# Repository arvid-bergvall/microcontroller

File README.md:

Basic microcontroller design using stm32f103t8c6 chip

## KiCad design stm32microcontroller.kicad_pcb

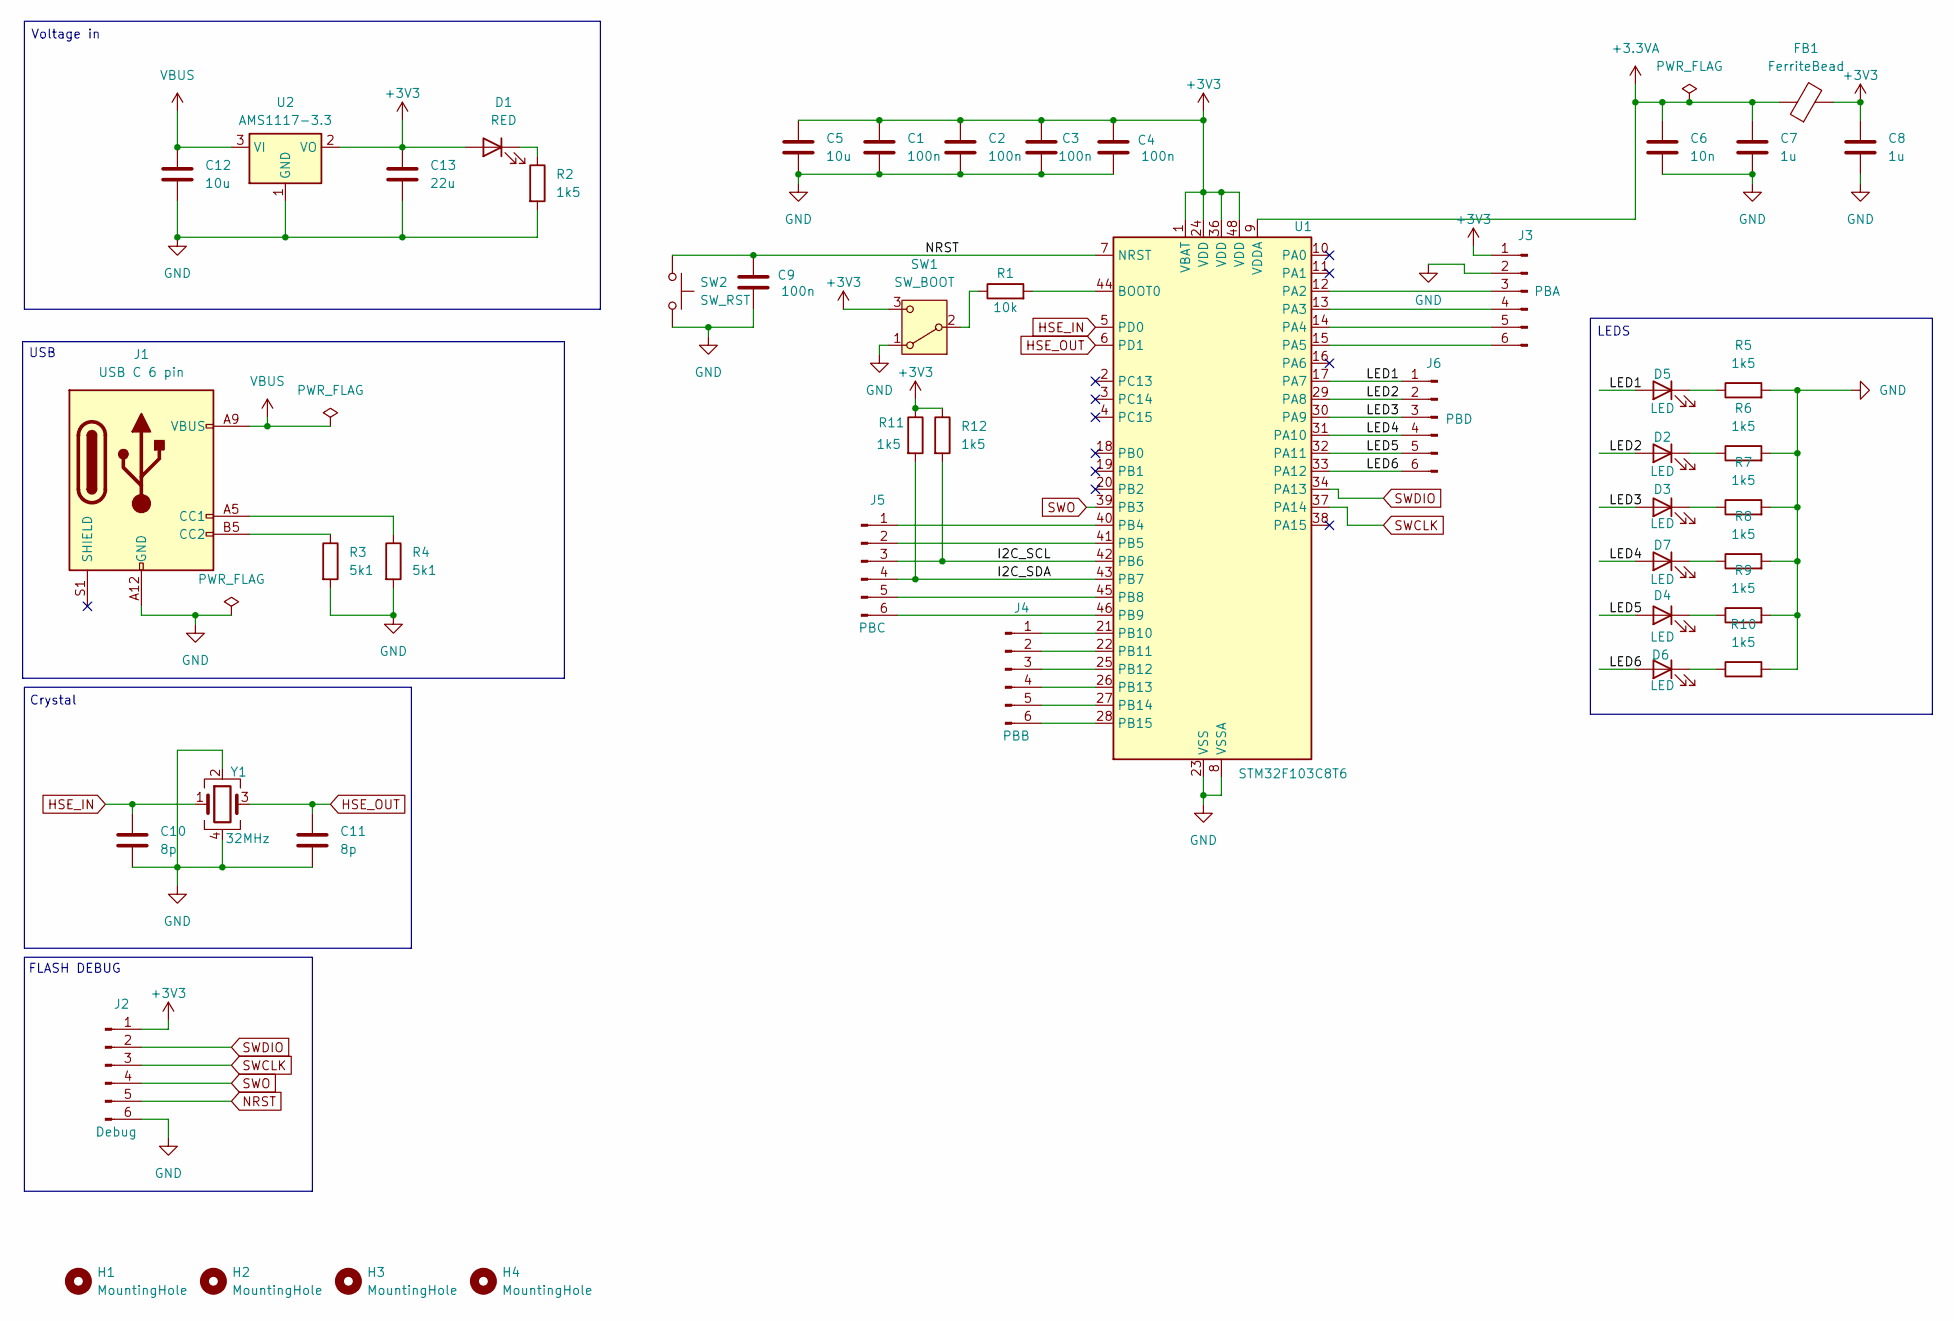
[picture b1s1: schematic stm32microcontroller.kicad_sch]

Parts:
C1, C2, C3, C4, C9: 100n; C_0603_1608Metric
C5, C12: 10u; C_0603_1608Metric
C6: 10n; C_0603_1608Metric
C7, C8: 1u; C_0603_1608Metric
C10, C11: 8p; C_0603_1608Metric
C13: 22u; C_0603_1608Metric
D1: RED; LED_0603_1608Metric
D2, D3, D4, D5, D6, D7: LED; LED_0603_1608Metric
FB1: FerriteBead; R_0805_2012Metric
H1, H2, H3, H4: MountingHole; MountingHole_2.2mm_M2
J1: USB C 6 pin; USB_C_Receptacle_GCT_USB4125-xx-x_6P_TopMnt_Horizontal
J2: Debug; PinHeader_2x03_P2.54mm_Vertical
J3: PBA; PinHeader_1x06_P2.54mm_Vertical
J4: PBB; PinHeader_1x06_P2.54mm_Vertical
J5: PBC; PinHeader_1x06_P2.54mm_Vertical
J6: PBD; PinHeader_1x06_P2.54mm_Vertical
R1: 10k; R_0603_1608Metric
R2, R5, R6, R7, R8, R9, R10, R11, R12: 1k5; R_0603_1608Metric
R3, R4: 5k1; R_0603_1608Metric
SW1: SW_BOOT; PinHeader_1x03_P2.54mm_Vertical
SW2: SW_RST; SW_DIP_SPSTx01_Slide_Copal_CHS-01A_W5.08mm_P1.27mm_JPin
U1: STM32F103C8T6; LQFP-48_7x7mm_P0.5mm
U2: AMS1117-3.3; SOT-223-3_TabPin2
Y1: 32MHz; Oscillator_SMD_Abracon_ASCO-4Pin_1.6x1.2mm

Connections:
+3.3VA: C6.1, C7.1, FB1.1, U1.9 (VDDA)
+3V3: C1.1, C2.1, C3.1, C4.1, C5.1, C8.1, C13.1, D1.2 (A), FB1.2, J2.1, J3.1, R11.1, R12.1, SW1.3 (C), U1.1 (VBAT), U1.24 (VDD), U1.36 (VDD), U1.48 (VDD), U2.2 (VO); also elsewhere on the board
/I2C_SCL: J5.3, R12.2, U1.42 (PB6)
/I2C_SDA: J5.4, R11.2, U1.43 (PB7)
/LED1: D5.2 (A), J6.1, U1.17 (PA7)
/LED2: D2.2 (A), J6.2, U1.29 (PA8)
/LED3: D3.2 (A), J6.3, U1.30 (PA9)
/LED4: D7.2 (A), J6.4, U1.31 (PA10)
/LED5: D4.2 (A), J6.5, U1.32 (PA11)
/LED6: D6.2 (A), J6.6, U1.33 (PA12)
GND: C1.2, C2.2, C3.2, C4.2, C5.2, C6.2, C7.2, C8.2, C9.2, C10.2, C11.2, C12.2, C13.2, J1.A12 (GND), J1.B12 (GND), J2.6, J3.2, R2.2, R3.2, R4.2, R5.2, R6.2, R7.2, R8.2, R9.2, R10.2, SW1.1 (A), SW2.2, U1.8 (VSSA), U1.23 (VSS), U1.35 (VSS), U1.47 (VSS), U2.1 (GND), Y1.2, Y1.4; also elsewhere on the board
HSE_IN: C10.1, U1.5 (PD0), Y1.1
HSE_OUT: C11.1, U1.6 (PD1), Y1.3
NRST: C9.1, SW2.1, U1.7 (NRST); also elsewhere on the board
unnamed: D1.1 (K), R2.1
unnamed: D2.1 (K), R6.1
unnamed: D3.1 (K), R7.1
unnamed: D4.1 (K), R9.1
unnamed: D5.1 (K), R5.1
unnamed: D6.1 (K), R10.1
unnamed: D7.1 (K), R8.1
unnamed: J1.A5 (CC1), R4.1
unnamed: J1.B5 (CC2), R3.1
unnamed: J3.3, U1.12 (PA2)
unnamed: J3.4, U1.13 (PA3)
unnamed: J3.5, U1.14 (PA4)
unnamed: J3.6, U1.15 (PA5)
unnamed: J4.1, U1.21 (PB10)
unnamed: J4.2, U1.22 (PB11)
unnamed: J4.3, U1.25 (PB12)
unnamed: J4.4, U1.26 (PB13)
unnamed: J4.5, U1.27 (PB14)
unnamed: J4.6, U1.28 (PB15)
unnamed: J5.1, U1.40 (PB4)
unnamed: J5.2, U1.41 (PB5)
unnamed: J5.5, U1.45 (PB8)
unnamed: J5.6, U1.46 (PB9)
unnamed 37: R1.1, SW1.2 (B); also elsewhere on the board
unnamed: R1.2, U1.44 (BOOT0)
SWCLK: J2.3, U1.37 (PA14); also elsewhere on the board
SWDIO: J2.2, U1.34 (PA13); also elsewhere on the board
SWO: J2.4, U1.39 (PB3); also elsewhere on the board
VBUS: C12.1, J1.A9 (VBUS), J1.B9 (VBUS), U2.3 (VI)

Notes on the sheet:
Crystal
Voltage in
LEDS
USB
FLASH DEBUG

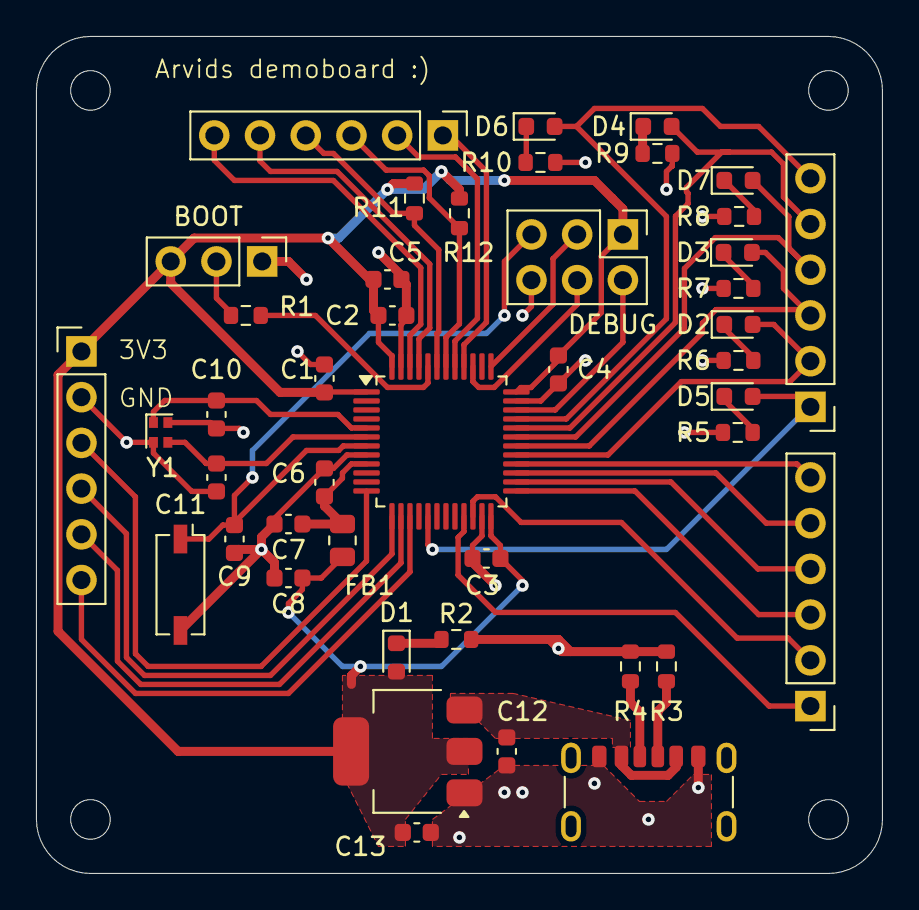
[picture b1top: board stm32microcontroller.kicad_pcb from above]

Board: 2 copper layers, 47.0 x 46.5 mm, 48 parts (0 on the bottom side), 43 nets.

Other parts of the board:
BOOT: SW_BOOT; PinHeader_1x03_P2.54mm_Vertical
DEBUG: Debug; PinHeader_2x03_P2.54mm_Vertical

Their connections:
+3V3: BOOT.3 (C), DEBUG.1; also elsewhere on the board
GND: BOOT.1 (A), DEBUG.6; also elsewhere on the board
NRST: DEBUG.5; also elsewhere on the board
unnamed 37: BOOT.2 (B); also elsewhere on the board
SWCLK: DEBUG.3; also elsewhere on the board
SWDIO: DEBUG.2; also elsewhere on the board
SWO: DEBUG.4; also elsewhere on the board

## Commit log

2024-11-07 Commit microntroller pcb and schematic
2024-11-07 added pictures of schematic and pcb
2024-11-07 added gerber files
